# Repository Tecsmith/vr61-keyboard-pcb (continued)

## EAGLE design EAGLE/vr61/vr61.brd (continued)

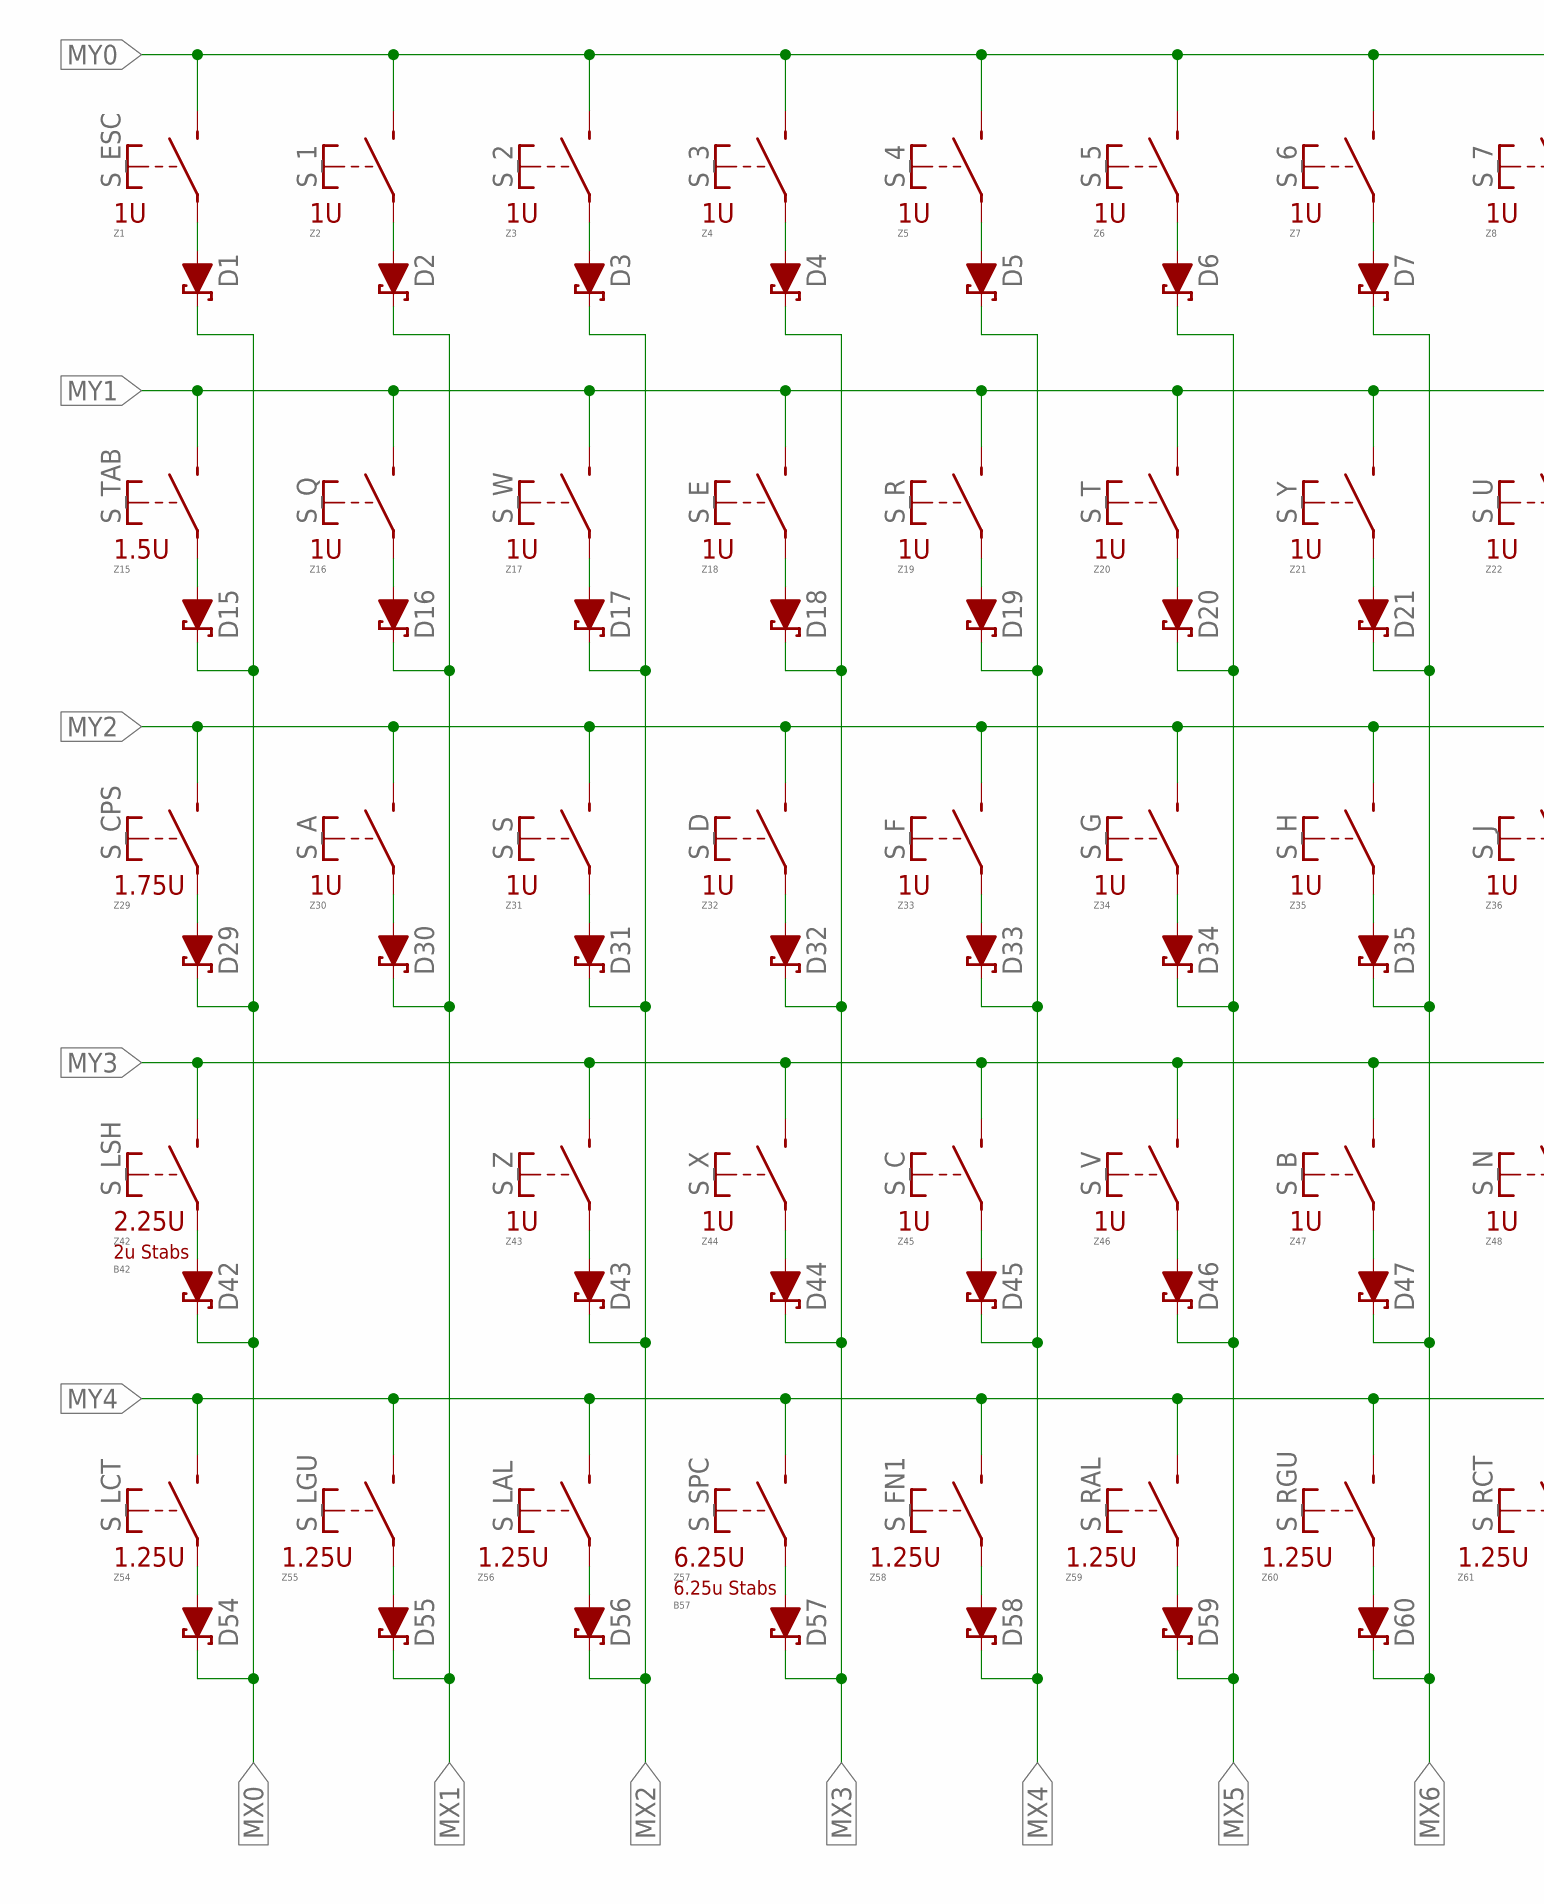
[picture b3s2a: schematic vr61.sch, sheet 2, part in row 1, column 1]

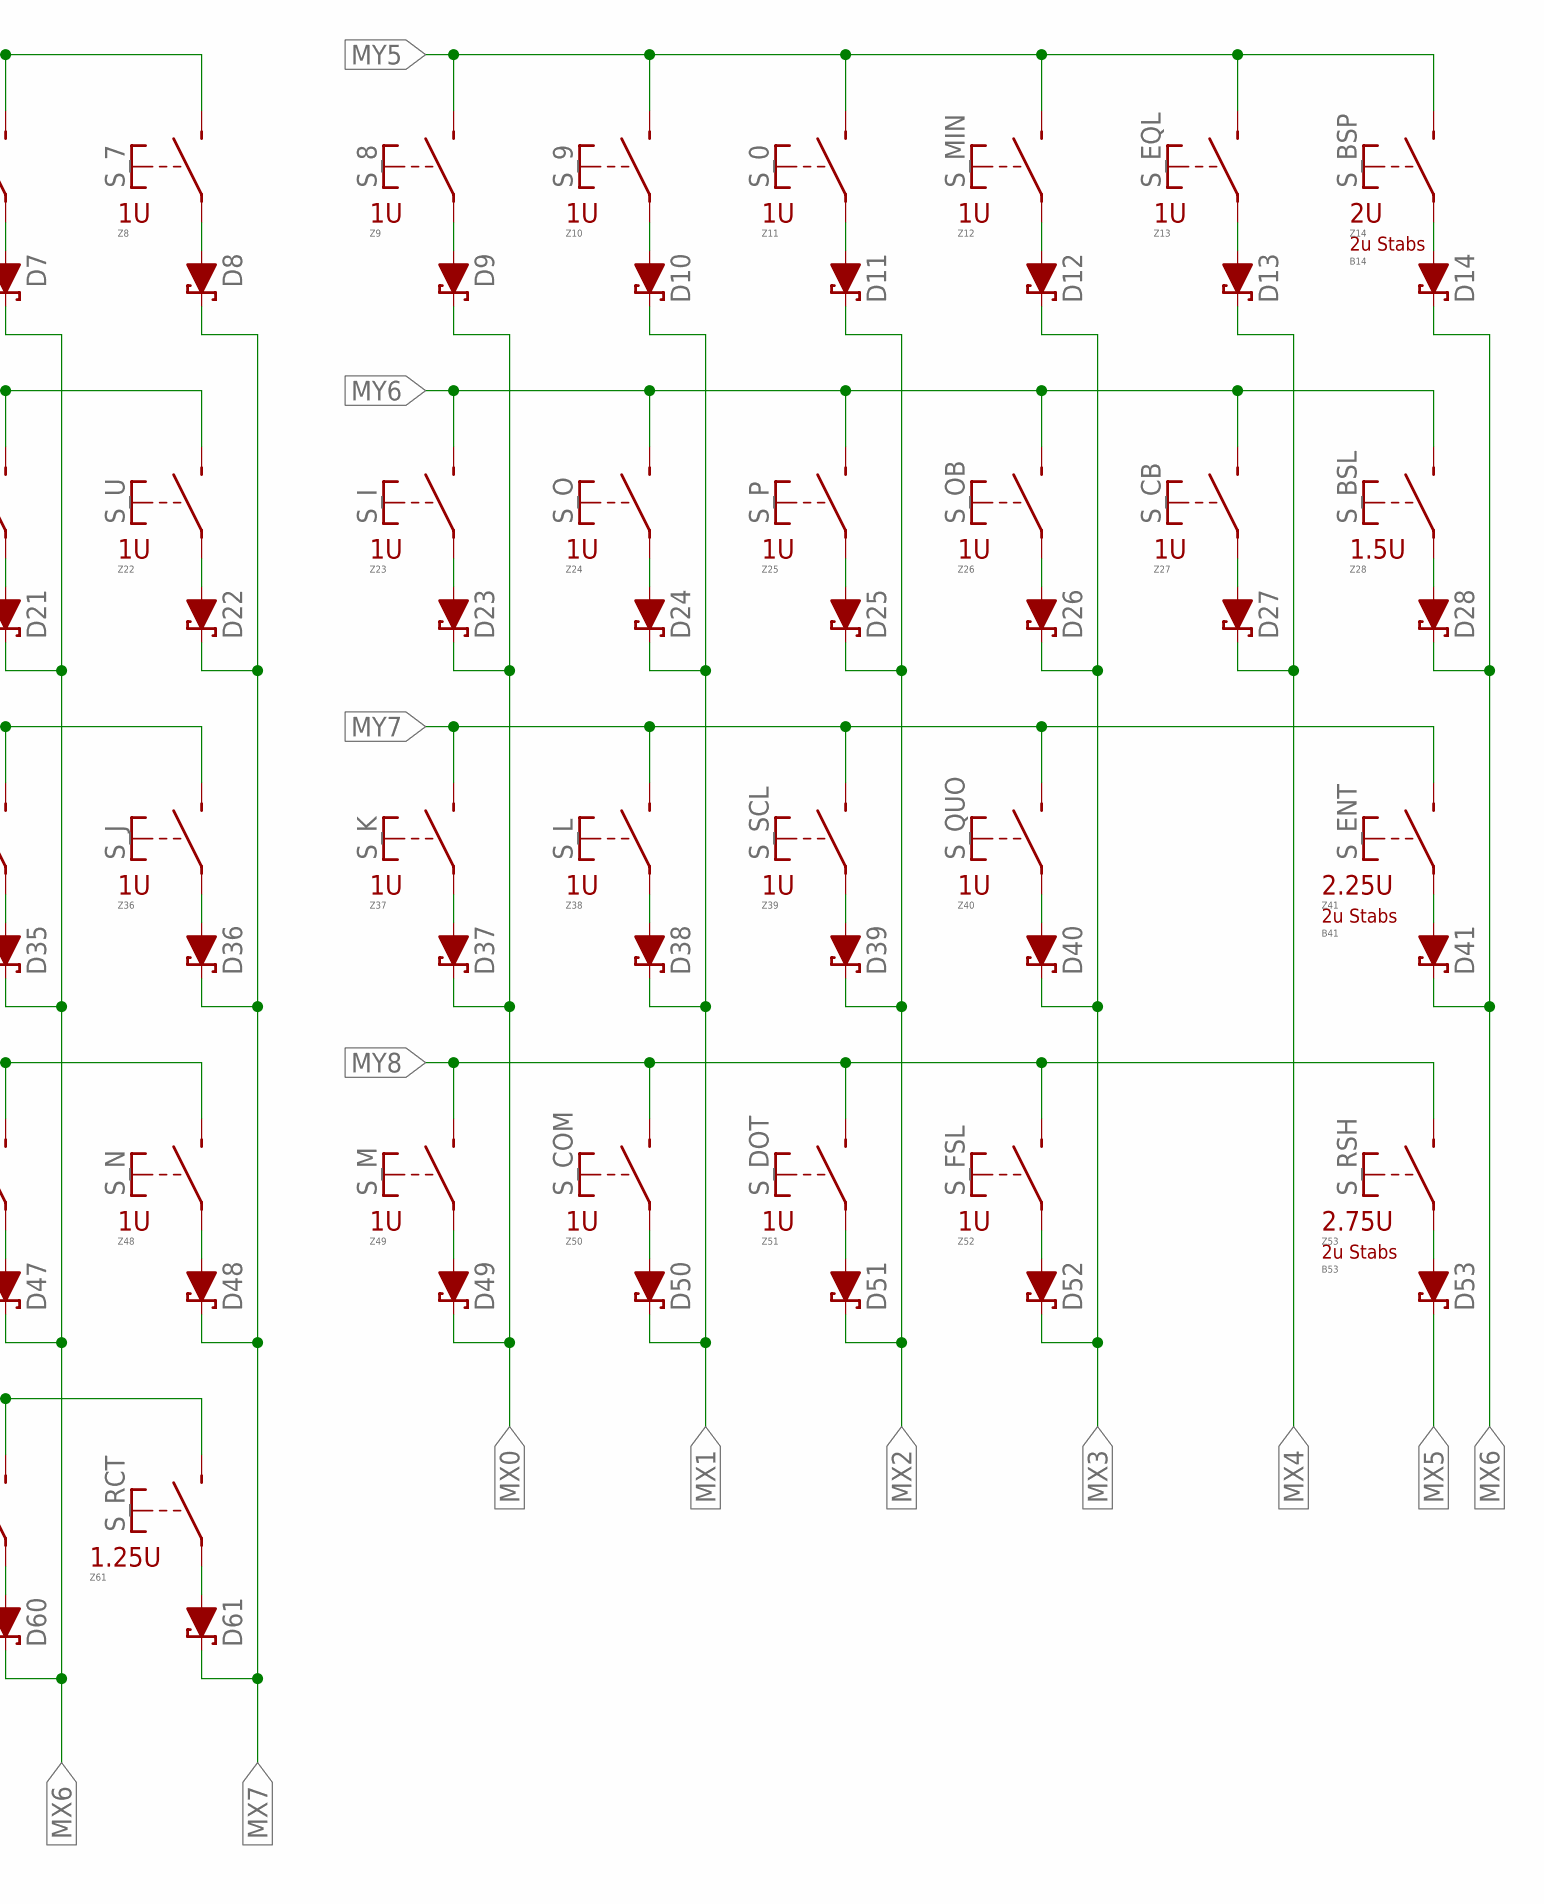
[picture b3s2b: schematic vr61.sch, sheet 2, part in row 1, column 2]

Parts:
B14, B41, B42, B53: MX-STABS-200U
B57: MX-STABS-625U
D1, D2, D3, D4, D5, D6, D7, D8, D9, D10, D11, D12, D13, D14, D15, D16, D17, D18, D19, D20, D21, D22, D23, D24, D25, D26, D27, D28, D29, D30, D31, D32, D33, D34, D35, D36, D37, D38, D39, D40, D41, D42, D43, D44, D45, D46, D47, D48, D49, D50, D51, D52, D53, D54, D55, D56, D57, D58, D59, D60, D61: 1N5819WS; SOD-123
S_0, S_1, S_2, S_3, S_4, S_5, S_6, S_7, S_8, S_9: MX-5-PIN-HOTSWAP-PAD
S_A: MX-5-PIN-HOTSWAP-PAD
S_B: MX-5-PIN-HOTSWAP-PAD
S_BSL: MX-5-PIN-HOTSWAP-PAD
S_BSP: MX-5-PIN-HOTSWAP-PAD
S_C: MX-5-PIN-HOTSWAP-PAD
S_CB: MX-5-PIN-HOTSWAP-PAD
S_COM: MX-5-PIN-HOTSWAP-PAD
S_CPS: MX-5-PIN-HOTSWAP-PAD
S_D: MX-5-PIN-HOTSWAP-PAD
S_DOT: MX-5-PIN-HOTSWAP-PAD
S_E: MX-5-PIN-HOTSWAP-PAD
S_ENT: MX-5-PIN-HOTSWAP-PAD
S_EQL: MX-5-PIN-HOTSWAP-PAD
S_ESC: MX-5-PIN-HOTSWAP-PAD
S_F: MX-5-PIN-HOTSWAP-PAD
S_FN1: MX-5-PIN-HOTSWAP-PAD
S_FSL: MX-5-PIN-HOTSWAP-PAD
S_G: MX-5-PIN-HOTSWAP-PAD
S_H: MX-5-PIN-HOTSWAP-PAD
S_I: MX-5-PIN-HOTSWAP-PAD
S_J: MX-5-PIN-HOTSWAP-PAD
S_K: MX-5-PIN-HOTSWAP-PAD
S_L: MX-5-PIN-HOTSWAP-PAD
S_LAL: MX-5-PIN-HOTSWAP-PAD
S_LCT: MX-5-PIN-HOTSWAP-PAD
S_LGU: MX-5-PIN-HOTSWAP-PAD
S_LSH: MX-5-PIN-HOTSWAP-PAD
S_M: MX-5-PIN-HOTSWAP-PAD
S_MIN: MX-5-PIN-HOTSWAP-PAD
S_N: MX-5-PIN-HOTSWAP-PAD
S_O: MX-5-PIN-HOTSWAP-PAD
S_OB: MX-5-PIN-HOTSWAP-PAD
S_P: MX-5-PIN-HOTSWAP-PAD
S_Q: MX-5-PIN-HOTSWAP-PAD
S_QUO: MX-5-PIN-HOTSWAP-PAD
S_R: MX-5-PIN-HOTSWAP-PAD
S_RAL: MX-5-PIN-HOTSWAP-PAD
S_RCT: MX-5-PIN-HOTSWAP-PAD
S_RGU: MX-5-PIN-HOTSWAP-PAD
S_RSH: MX-5-PIN-HOTSWAP-PAD
S_S: MX-5-PIN-HOTSWAP-PAD
S_SCL: MX-5-PIN-HOTSWAP-PAD
S_SPC: MX-5-PIN-HOTSWAP-PAD
S_T: MX-5-PIN-HOTSWAP-PAD
S_TAB: MX-5-PIN-HOTSWAP-PAD
S_U: MX-5-PIN-HOTSWAP-PAD
S_V: MX-5-PIN-HOTSWAP-PAD
S_W: MX-5-PIN-HOTSWAP-PAD
S_X: MX-5-PIN-HOTSWAP-PAD
S_Y: MX-5-PIN-HOTSWAP-PAD
S_Z: MX-5-PIN-HOTSWAP-PAD
Z1, Z2, Z3, Z4, Z5, Z6, Z7, Z8, Z9, Z10, Z11, Z12, Z13, Z16, Z17, Z18, Z19, Z20, Z21, Z22, Z23, Z24, Z25, Z26, Z27, Z30, Z31, Z32, Z33, Z34, Z35, Z36, Z37, Z38, Z39, Z40, Z43, Z44, Z45, Z46, Z47, Z48, Z49, Z50, Z51, Z52: MX-FPRINT-100U19; MX-FPRINT-1900-100U
Z14: MX-FPRINT-200U19; MX-FPRINT-1900-200U
Z15, Z28: MX-FPRINT-150U19; MX-FPRINT-1900-150U
Z29: MX-FPRINT-175U19; MX-FPRINT-1900-175U
Z41, Z42: MX-FPRINT-225U19; MX-FPRINT-1900-225U
Z53: MX-FPRINT-275U19; MX-FPRINT-1900-275U
Z54, Z55, Z56, Z58, Z59, Z60, Z61: MX-FPRINT-125U19; MX-FPRINT-1900-125U
Z57: MX-FPRINT-625U19; MX-FPRINT-1900-625U

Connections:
MX0: D1.C, D9.C, D15.C, D23.C, D29.C, D37.C, D42.C, D49.C, D54.C; also elsewhere on the board
MX1: D2.C, D10.C, D16.C, D24.C, D30.C, D38.C, D50.C, D55.C; also elsewhere on the board
MX2: D3.C, D11.C, D17.C, D25.C, D31.C, D39.C, D43.C, D51.C, D56.C; also elsewhere on the board
MX3: D4.C, D12.C, D18.C, D26.C, D32.C, D40.C, D44.C, D52.C, D57.C; also elsewhere on the board
MX4: D5.C, D13.C, D19.C, D27.C, D33.C, D45.C, D58.C; also elsewhere on the board
MX5: D6.C, D20.C, D34.C, D46.C, D53.C, D59.C; also elsewhere on the board
MX6: D7.C, D14.C, D21.C, D28.C, D35.C, D41.C, D47.C, D60.C; also elsewhere on the board
MX7: D8.C, D22.C, D36.C, D48.C, D61.C; also elsewhere on the board
MY0: S_1.P$2 (S), S_1.P$4 (S), S_2.P$2 (S), S_2.P$4 (S), S_3.P$2 (S), S_3.P$4 (S), S_4.P$2 (S), S_4.P$4 (S), S_5.P$2 (S), S_5.P$4 (S), S_6.P$2 (S), S_6.P$4 (S), S_7.P$2 (S), S_7.P$4 (S), S_ESC.P$2 (S), S_ESC.P$4 (S); also elsewhere on the board
MY1: S_E.P$2 (S), S_E.P$4 (S), S_Q.P$2 (S), S_Q.P$4 (S), S_R.P$2 (S), S_R.P$4 (S), S_T.P$2 (S), S_T.P$4 (S), S_TAB.P$2 (S), S_TAB.P$4 (S), S_U.P$2 (S), S_U.P$4 (S), S_W.P$2 (S), S_W.P$4 (S), S_Y.P$2 (S), S_Y.P$4 (S); also elsewhere on the board
MY2: S_A.P$2 (S), S_A.P$4 (S), S_CPS.P$2 (S), S_CPS.P$4 (S), S_D.P$2 (S), S_D.P$4 (S), S_F.P$2 (S), S_F.P$4 (S), S_G.P$2 (S), S_G.P$4 (S), S_H.P$2 (S), S_H.P$4 (S), S_J.P$2 (S), S_J.P$4 (S), S_S.P$2 (S), S_S.P$4 (S); also elsewhere on the board
MY3: S_B.P$2 (S), S_B.P$4 (S), S_C.P$2 (S), S_C.P$4 (S), S_LSH.P$2 (S), S_LSH.P$4 (S), S_N.P$2 (S), S_N.P$4 (S), S_V.P$2 (S), S_V.P$4 (S), S_X.P$2 (S), S_X.P$4 (S), S_Z.P$2 (S), S_Z.P$4 (S); also elsewhere on the board
MY4: S_FN1.P$2 (S), S_FN1.P$4 (S), S_LAL.P$2 (S), S_LAL.P$4 (S), S_LCT.P$2 (S), S_LCT.P$4 (S), S_LGU.P$2 (S), S_LGU.P$4 (S), S_RAL.P$2 (S), S_RAL.P$4 (S), S_RCT.P$2 (S), S_RCT.P$4 (S), S_RGU.P$2 (S), S_RGU.P$4 (S), S_SPC.P$2 (S), S_SPC.P$4 (S); also elsewhere on the board
MY5: S_0.P$2 (S), S_0.P$4 (S), S_8.P$2 (S), S_8.P$4 (S), S_9.P$2 (S), S_9.P$4 (S), S_BSP.P$2 (S), S_BSP.P$4 (S), S_EQL.P$2 (S), S_EQL.P$4 (S), S_MIN.P$2 (S), S_MIN.P$4 (S); also elsewhere on the board
MY6: S_BSL.P$2 (S), S_BSL.P$4 (S), S_CB.P$2 (S), S_CB.P$4 (S), S_I.P$2 (S), S_I.P$4 (S), S_O.P$2 (S), S_O.P$4 (S), S_OB.P$2 (S), S_OB.P$4 (S), S_P.P$2 (S), S_P.P$4 (S); also elsewhere on the board
MY7: S_ENT.P$2 (S), S_ENT.P$4 (S), S_K.P$2 (S), S_K.P$4 (S), S_L.P$2 (S), S_L.P$4 (S), S_QUO.P$2 (S), S_QUO.P$4 (S), S_SCL.P$2 (S), S_SCL.P$4 (S); also elsewhere on the board
MY8: S_COM.P$2 (S), S_COM.P$4 (S), S_DOT.P$2 (S), S_DOT.P$4 (S), S_FSL.P$2 (S), S_FSL.P$4 (S), S_M.P$2 (S), S_M.P$4 (S), S_RSH.P$2 (S), S_RSH.P$4 (S); also elsewhere on the board
unnamed: D1.A, S_ESC.P$1, S_ESC.P$3
unnamed: D2.A, S_1.P$1, S_1.P$3
unnamed: D3.A, S_2.P$1, S_2.P$3
unnamed: D4.A, S_3.P$1, S_3.P$3
unnamed: D5.A, S_4.P$1, S_4.P$3
unnamed: D6.A, S_5.P$1, S_5.P$3
unnamed: D7.A, S_6.P$1, S_6.P$3
unnamed: D8.A, S_7.P$1, S_7.P$3
unnamed: D9.A, S_8.P$1, S_8.P$3
unnamed: D10.A, S_9.P$1, S_9.P$3
unnamed: D11.A, S_0.P$1, S_0.P$3
unnamed: D12.A, S_MIN.P$1, S_MIN.P$3
unnamed: D13.A, S_EQL.P$1, S_EQL.P$3
unnamed: D14.A, S_BSP.P$1, S_BSP.P$3
unnamed: D15.A, S_TAB.P$1, S_TAB.P$3
unnamed: D16.A, S_Q.P$1, S_Q.P$3
unnamed: D17.A, S_W.P$1, S_W.P$3
unnamed: D18.A, S_E.P$1, S_E.P$3
unnamed: D19.A, S_R.P$1, S_R.P$3
unnamed: D20.A, S_T.P$1, S_T.P$3
unnamed: D21.A, S_Y.P$1, S_Y.P$3
unnamed: D22.A, S_U.P$1, S_U.P$3
unnamed: D23.A, S_I.P$1, S_I.P$3
unnamed: D24.A, S_O.P$1, S_O.P$3
unnamed: D25.A, S_P.P$1, S_P.P$3
unnamed: D26.A, S_OB.P$1, S_OB.P$3
unnamed: D27.A, S_CB.P$1, S_CB.P$3
unnamed: D28.A, S_BSL.P$1, S_BSL.P$3
unnamed: D30.A, S_A.P$1, S_A.P$3
unnamed: D31.A, S_S.P$1, S_S.P$3
unnamed: D32.A, S_D.P$1, S_D.P$3
unnamed: D33.A, S_F.P$1, S_F.P$3
unnamed: D34.A, S_G.P$1, S_G.P$3
unnamed: D35.A, S_H.P$1, S_H.P$3
unnamed: D36.A, S_J.P$1, S_J.P$3
unnamed: D37.A, S_K.P$1, S_K.P$3
unnamed: D38.A, S_L.P$1, S_L.P$3
unnamed: D39.A, S_SCL.P$1, S_SCL.P$3
unnamed: D40.A, S_QUO.P$1, S_QUO.P$3
unnamed: D41.A, S_ENT.P$1, S_ENT.P$3
unnamed: D42.A, S_LSH.P$1, S_LSH.P$3
unnamed: D43.A, S_Z.P$1, S_Z.P$3
unnamed: D44.A, S_X.P$1, S_X.P$3
unnamed: D45.A, S_C.P$1, S_C.P$3
unnamed: D46.A, S_V.P$1, S_V.P$3
unnamed: D47.A, S_B.P$1, S_B.P$3
unnamed: D48.A, S_N.P$1, S_N.P$3
unnamed: D49.A, S_M.P$1, S_M.P$3
unnamed: D50.A, S_COM.P$1, S_COM.P$3
unnamed: D51.A, S_DOT.P$1, S_DOT.P$3
unnamed: D52.A, S_FSL.P$1, S_FSL.P$3
unnamed: D53.A, S_RSH.P$1, S_RSH.P$3
unnamed: D54.A, S_LCT.P$1, S_LCT.P$3
unnamed: D55.A, S_LGU.P$1, S_LGU.P$3
unnamed: D56.A, S_LAL.P$1, S_LAL.P$3
unnamed: D57.A, S_SPC.P$1, S_SPC.P$3
unnamed: D58.A, S_FN1.P$1, S_FN1.P$3
unnamed: D59.A, S_RAL.P$1, S_RAL.P$3
unnamed: D60.A, S_RGU.P$1, S_RGU.P$3
unnamed: D61.A, S_RCT.P$1, S_RCT.P$3
unnamed: D29.A, S_CPS.P$1, S_CPS.P$3

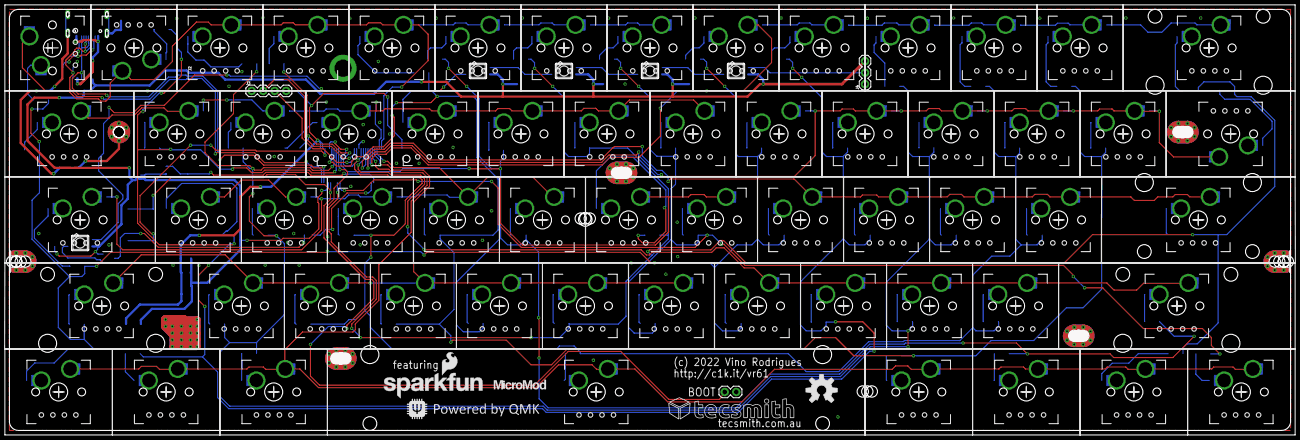
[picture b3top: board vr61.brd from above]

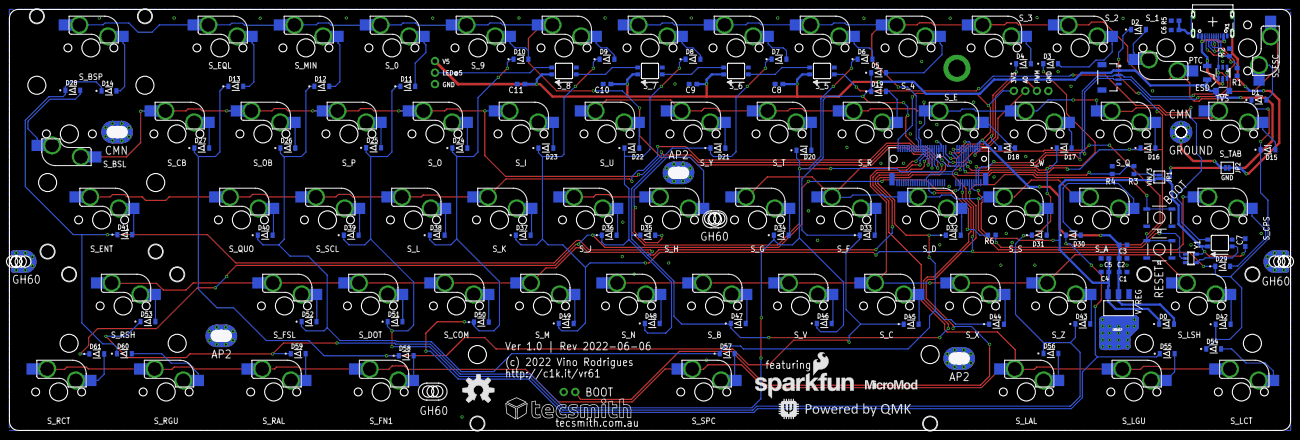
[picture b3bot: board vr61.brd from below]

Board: 2 copper layers, 280.7 x 90.7 mm, 244 parts (96 on the bottom side), 108 nets.

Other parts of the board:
LOGO2: OSHW-LOGOL; OSHW-LOGO-L
U$7: TECSMITH-LOGOLONG; TECSMITH-NAME
U$10: SPARKFUN_LOGO0.2; SFE_LOGO_NAME_FLAME_.2
U$12: QMK_LOGO
U$13: MICROMOD-LOGO

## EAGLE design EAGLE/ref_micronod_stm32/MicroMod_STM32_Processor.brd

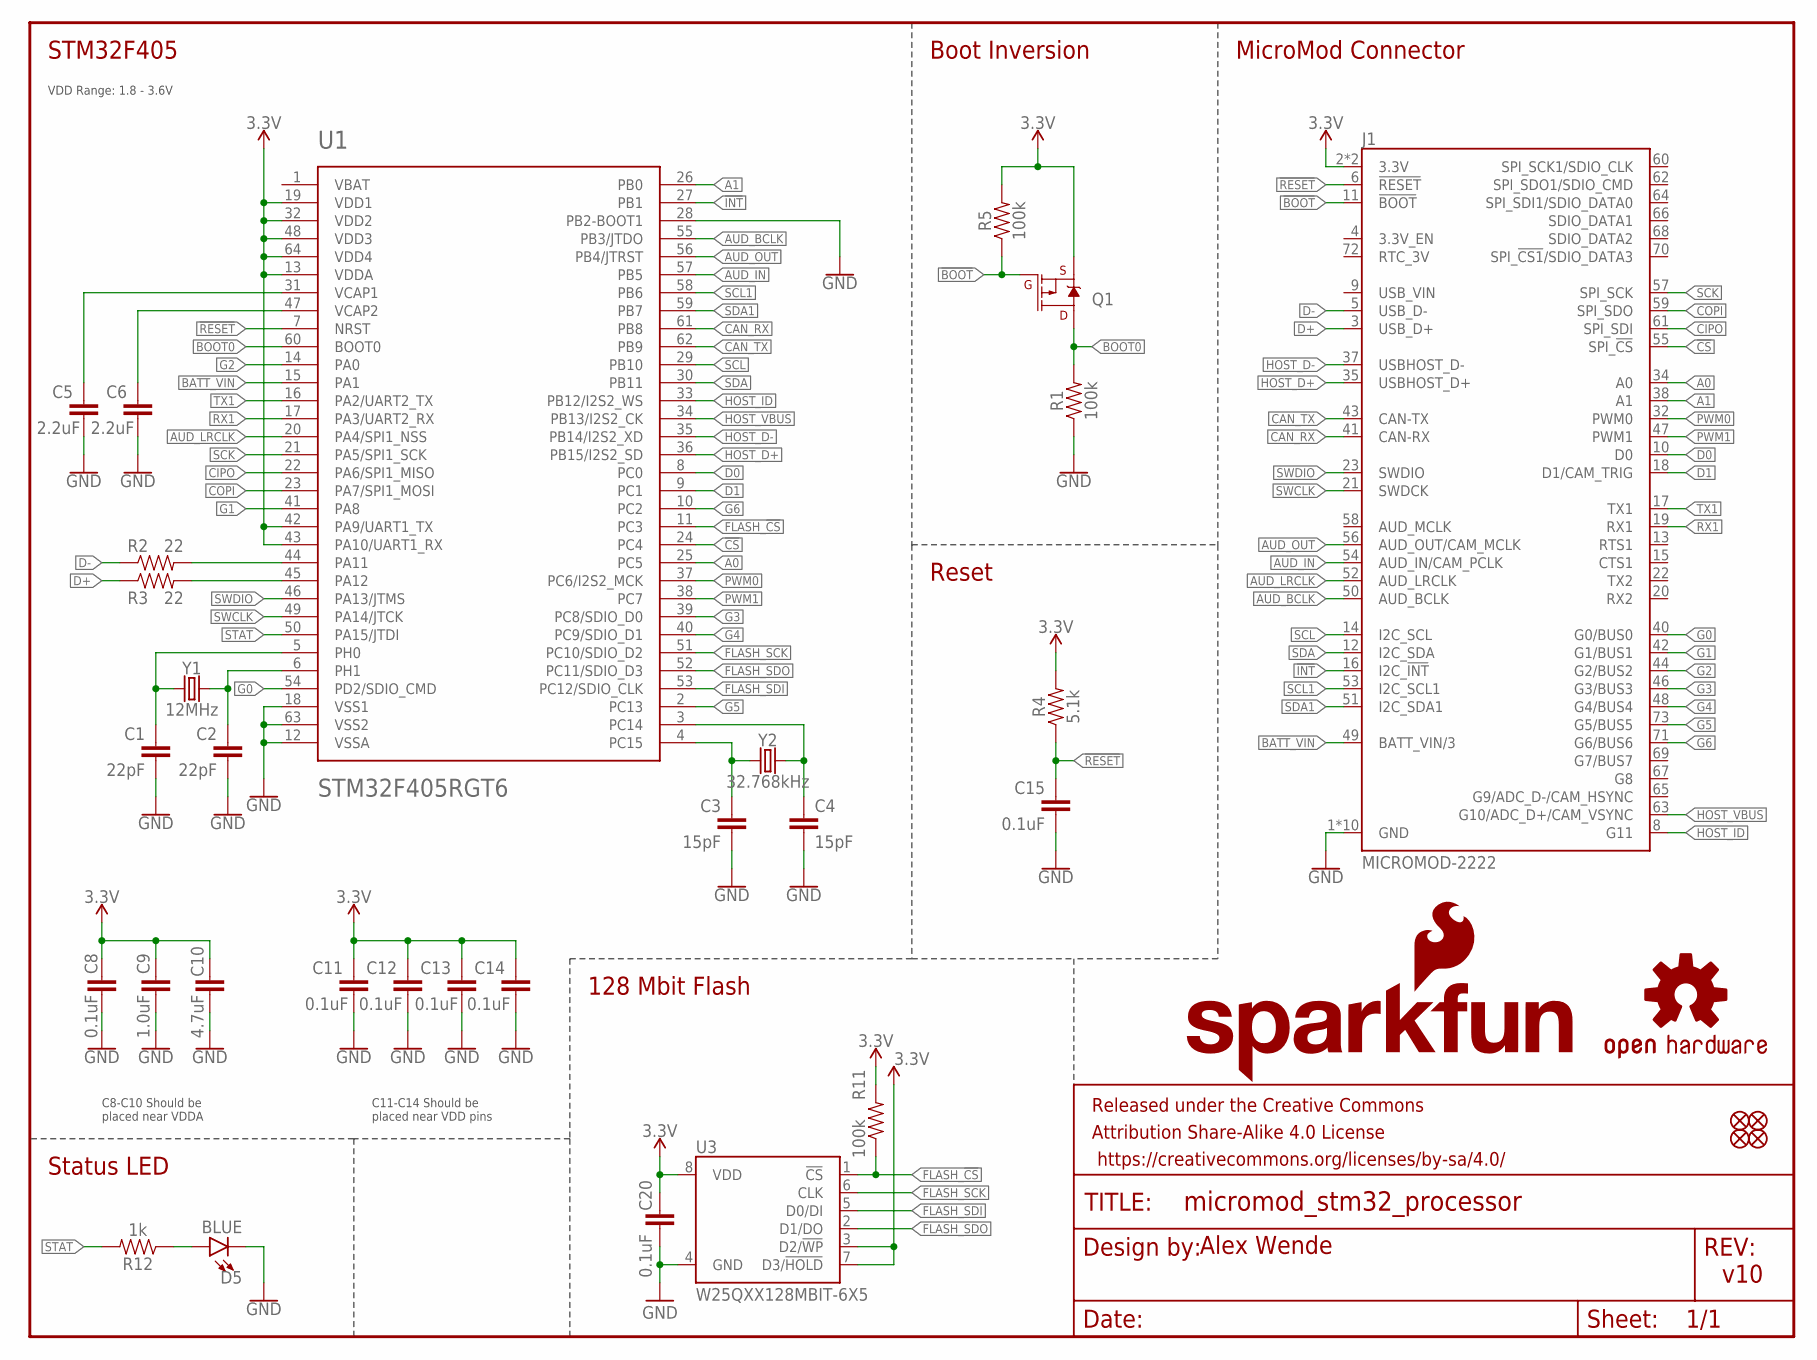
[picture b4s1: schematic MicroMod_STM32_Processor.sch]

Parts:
C1, C2: 22pF; 0402-TIGHT
C3, C4: 15pF; 0402-TIGHT
C5, C6: 2.2uF; 0402-TIGHT
C8, C11, C12, C13, C14, C15, C20: 0.1uF; 0402-TIGHT
C9: 1.0uF; 0402-TIGHT
C10: 4.7uF; 0402-TIGHT
D5: BLUE; LED-0603
FD1, FD2, FD3, FD4: FIDUCIALUFIDUCIAL; FIDUCIAL-MICRO
FRAME1: FRAME-LETTER; CREATIVE_COMMONS
J1: MICROMOD-2222; M.2-CARD-E-22
LOGO2: OSHW-LOGOS; OSHW-LOGO-S
LOGO3: SFE_LOGO_NAME_FLAME.1_INCH; SFE_LOGO_NAME_FLAME_.1
Q1: MOSFET_PCH-DMG2305UX-7; SOT23-3
R1, R5, R11: 100k; 0402-TIGHT
R2, R3: 22; 0402-TIGHT
R4: 5.1k; 0402-TIGHT
R12: 1k; 0402-TIGHT
U1: STM32F405RGT6; TQFP64
U3: W25QXX128MBIT-6X5; WSON-8-6X5
Y1: 12MHz; CRYSTAL-SMD-5X3.2-4PAD
Y2: 32.768kHz; CRYSTAL-SMD-3.2X1.5MM

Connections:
3.3V: C8.1, C9.1, C10.1, C11.1, C12.1, C13.1, C14.1, C20.1, J1.2 (3.3V), J1.74 (3.3V), Q1.2 (S), R4.2, R5.2, R11.2, U1.13 (VDDA), U1.19 (VDD1), U1.32 (VDD2), U1.42 (PA9/UART1_TX), U1.43 (PA10/UART1_RX), U1.48 (VDD3), U1.64 (VDD4), U3.3 (D2/!WP!), U3.7 (D3/!HOLD!), U3.8 (VDD)
!BOOT: J1.11 (!BOOT!), Q1.1 (G), R5.1
!CS: J1.55 (SPI_!CS!), U1.24 (PC4)
!INT: J1.16 (I2C_!INT!), U1.27 (PB1)
!RESET: C15.1, J1.6 (!RESET!), R4.1, U1.7 (NRST)
A0: J1.34 (A0), U1.25 (PC5)
A1: J1.38 (A1), U1.26 (PB0)
AUD_BCLK: J1.50 (AUD_BCLK), U1.55 (PB3/JTDO)
AUD_IN: J1.54 (AUD_IN/CAM_PCLK), U1.57 (PB5)
AUD_LRCLK: J1.52 (AUD_LRCLK), U1.20 (PA4/SPI1_NSS)
AUD_OUT: J1.56 (AUD_OUT/CAM_MCLK), U1.56 (PB4/JTRST)
BATT_VIN: J1.49 (BATT_VIN/3), U1.15 (PA1)
BOOT0: Q1.3 (D), R1.2, U1.60 (BOOT0)
CAN_RX: J1.41 (CAN-RX), U1.61 (PB8)
CAN_TX: J1.43 (CAN-TX), U1.62 (PB9)
CIPO: J1.61 (SPI_SDI), U1.22 (PA6/SPI1_MISO)
COPI: J1.59 (SPI_SDO), U1.23 (PA7/SPI1_MOSI)
D0: J1.10 (D0), U1.8 (PC0)
D1: J1.18 (D1/CAM_TRIG), U1.9 (PC1)
D+: J1.3 (USB_D+), R3.1
D-: J1.5 (USB_D-), R2.1
FLASH_!CS: R11.1, U1.11 (PC3), U3.1 (!CS!)
FLASH_SCK: U1.51 (PC10/SDIO_D2), U3.6 (CLK)
FLASH_SDI: U1.53 (PC12/SDIO_CLK), U3.5 (D0/DI)
FLASH_SDO: U1.52 (PC11/SDIO_D3), U3.2 (D1/DO)
G0: J1.40 (G0/BUS0), U1.54 (PD2/SDIO_CMD)
G1: J1.42 (G1/BUS1), U1.41 (PA8)
G2: J1.44 (G2/BUS2), U1.14 (PA0)
G3: J1.46 (G3/BUS3), U1.39 (PC8/SDIO_D0)
G4: J1.48 (G4/BUS4), U1.40 (PC9/SDIO_D1)
G5: J1.73 (G5/BUS5), U1.2 (PC13)
G6: J1.71 (G6/BUS6), U1.10 (PC2)
GND: C1.2, C2.2, C3.2, C4.2, C5.2, C6.2, C8.2, C9.2, C10.2, C11.2, C12.2, C13.2, C14.2, C15.2, C20.2, D5.C, J1.1 (GND), J1.7 (GND), J1.33 (GND), J1.36 (GND), J1.39 (GND), J1.45 (GND), J1.75 (GND), J1.GND1 (GND), J1.GND2 (GND), J1.GND3 (GND), R1.1, U1.12 (VSSA), U1.18 (VSS1), U1.28 (PB2-BOOT1), U1.63 (VSS2), U3.4 (GND)
HOST_D+: J1.35 (USBHOST_D+), U1.36 (PB15/I2S2_SD)
HOST_D-: J1.37 (USBHOST_D-), U1.35 (PB14/I2S2_XD)
HOST_ID: J1.8 (G11), U1.33 (PB12/I2S2_WS)
HOST_VBUS: J1.63 (G10/ADC_D+/CAM_VSYNC), U1.34 (PB13/I2S2_CK)
unnamed: D5.A, R12.1
unnamed: R2.2, U1.44 (PA11)
unnamed: R3.2, U1.45 (PA12)
unnamed: C4.1, U1.3 (PC14), Y2.P$2 (2)
unnamed: C3.1, U1.4 (PC15), Y2.P$1 (1)
unnamed: C2.1, U1.6 (PH1), Y1.3 (2)
unnamed: C1.1, U1.5 (PH0), Y1.1
unnamed: C6.1, U1.47 (VCAP2)
unnamed: C5.1, U1.31 (VCAP1)
PWM0: J1.32 (PWM0), U1.37 (PC6/I2S2_MCK)
PWM1: J1.47 (PWM1), U1.38 (PC7)
RX1: J1.19 (RX1), U1.17 (PA3/UART2_RX)
SCK: J1.57 (SPI_SCK), U1.21 (PA5/SPI1_SCK)
SCL: J1.14 (I2C_SCL), U1.29 (PB10)
SCL1: J1.53 (I2C_SCL1), U1.58 (PB6)
SDA: J1.12 (I2C_SDA), U1.30 (PB11)
SDA1: J1.51 (I2C_SDA1), U1.59 (PB7)
STAT: R12.2, U1.50 (PA15/JTDI)
SWCLK: J1.21 (SWDCK), U1.49 (PA14/JTCK)
SWDIO: J1.23 (SWDIO), U1.46 (PA13/JTMS)
TX1: J1.17 (TX1), U1.16 (PA2/UART2_TX)

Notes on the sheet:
128 Mbit Flash
Status LED
C11-C14 Should be placed near VDD pins
C8-C10 Should be placed near VDDA
Boot Inversion
Reset
MicroMod Connector
STM32F405
v10
Alex Wende
VDD Range: 1.8 - 3.6V

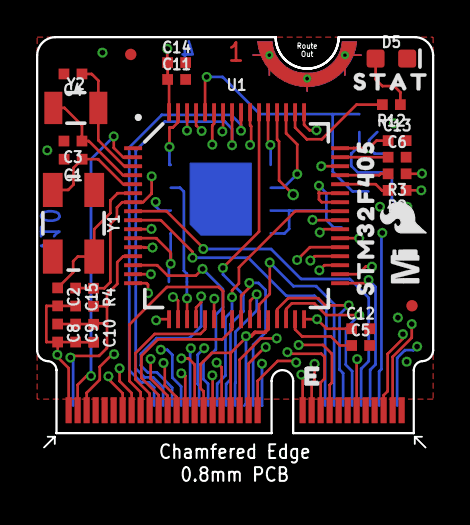
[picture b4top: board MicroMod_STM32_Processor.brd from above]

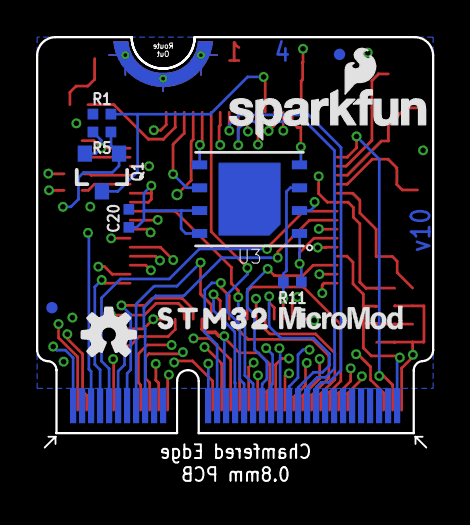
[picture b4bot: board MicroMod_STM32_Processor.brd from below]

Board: 4 copper layers, 22.0 x 25.0 mm, 43 parts (12 on the bottom side), 58 nets.

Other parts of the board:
U$1: STAT0
U$2: STM320
U$3: MICROMOD_MI_LOGO_.35
U$4: STM32F4050
U$5: MICROMOD_LOGO_.3
U$6: SFE_LOGO_FLAME_.1
U$7: PRODUCTION_INSTRUCTIONS
